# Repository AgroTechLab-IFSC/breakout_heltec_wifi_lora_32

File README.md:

# Breakout Board for Heltec WiFi Lora 32
Breakout board for [Heltec WiFi LoRa 32](https://docs.heltec.org/en/node/esp32/wifi_lora_32/index.html):
 - [Heltec WiFi LoRa 32 V2 board](https://heltec.org/project/wifi-lora-32v2);
 - [Heltec WiFi LoRa 32 V3 board](https://heltec.org/project/wifi-lora-32-v3);

## PCB Features
The breakout PCB has a dimension of 100mm x 100mm and 2 layers.

Project files:
 - [Schematic](./schematic.pdf)
 - [Gerber](./gerber.zip)

## 3D Images

## PCB Images

<div style="text-align:center;">
   <br><hr>
   <p>All rights reserved. &copy; Since 2020.<br>
   <b><a href="https://agrotechlab.lages.ifsc.edu.br/">AgroTechLab (<i>Agribusiness Technology Development Laboratory</i>)</a></b><br>
   <b><a href="https://ifsc.edu.br/web/campus-lages">IFSC (<i>Federal Institute of Santa Catarina</i>) - Campus Lages</a></b><br>
   225 Heitor Vila Lobos St., San Francisco<br>
   Lages/SC - Brazil<br>
   88506-400</p>
</div>

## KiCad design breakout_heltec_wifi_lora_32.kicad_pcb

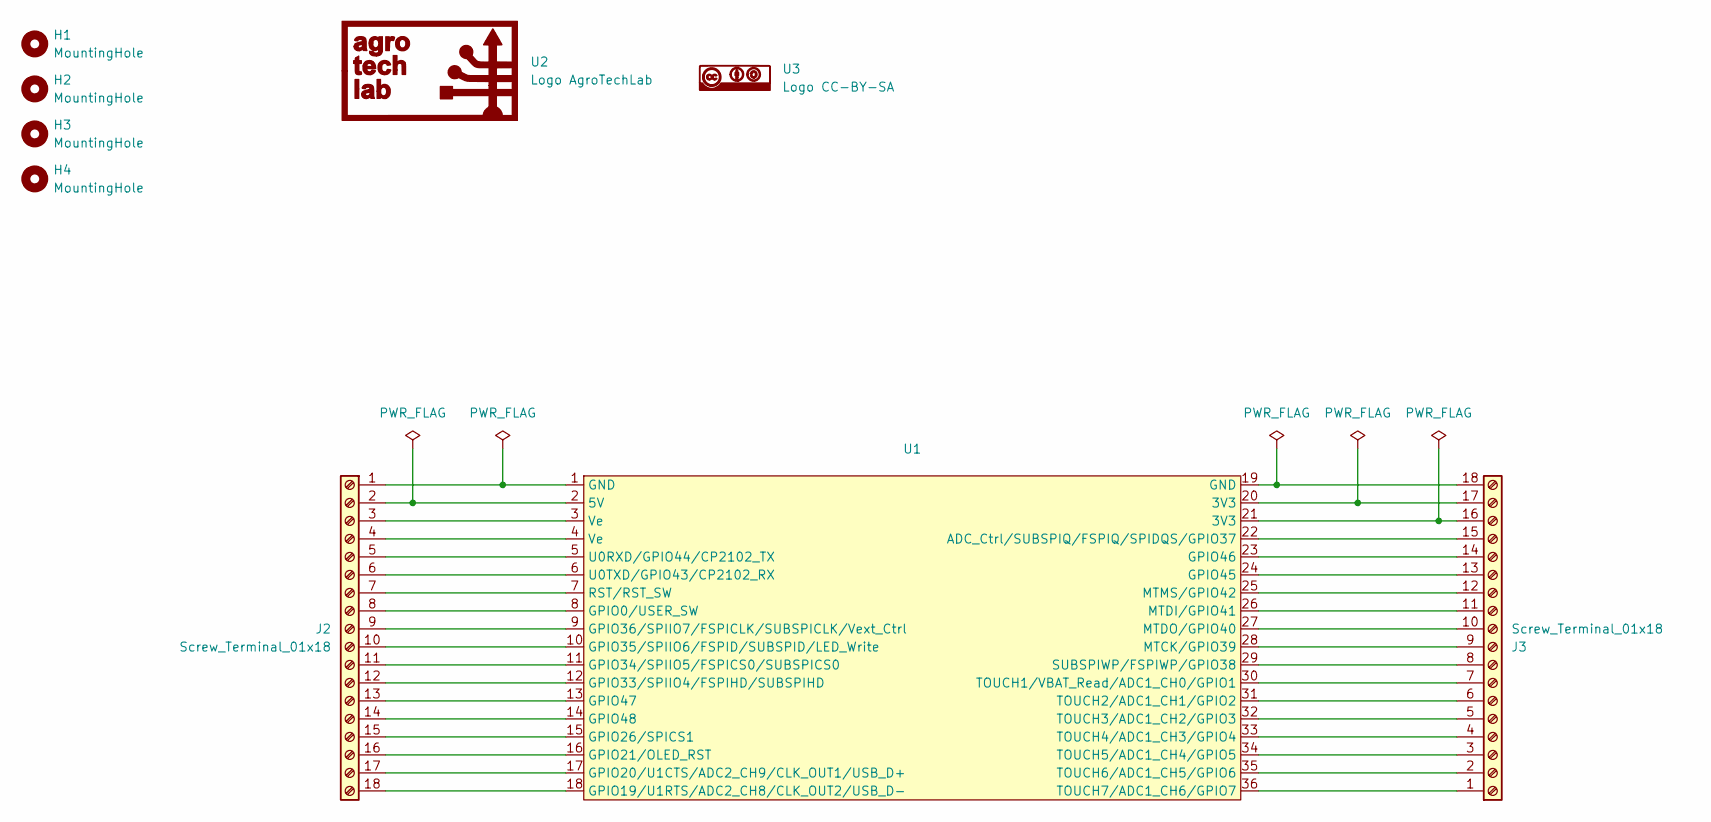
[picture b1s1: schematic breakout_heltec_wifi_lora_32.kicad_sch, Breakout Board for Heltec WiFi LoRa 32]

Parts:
H1, H2, H3, H4: MountingHole; MountingHole_3.2mm_M3_Pad_Via
J2, J3: Screw_Terminal_01x18; TE_1-282856-8
U1: Heltec WiFi LoRa 32 V3
U2: Logo AgroTechLab
U3: Logo CC-BY-SA

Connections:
unnamed: J2.1, U1.1 (GND)
unnamed: J2.2, U1.2 (5V)
unnamed: J2.3, U1.3 (Ve)
unnamed: J2.4, U1.4 (Ve)
unnamed: J2.5, U1.5 (U0RXD/GPIO44/CP2102_TX)
unnamed: J2.6, U1.6 (U0TXD/GPIO43/CP2102_RX)
unnamed: J2.7, U1.7 (RST/RST_SW)
unnamed: J2.8, U1.8 (GPIO0/USER_SW)
unnamed: J2.9, U1.9 (GPIO36/SPIIO7/FSPICLK/SUBSPICLK/Vext_Ct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)
unnamed: J2.10, U1.10 (GPIO35/SPIIO6/FSPID/SUBSPID/LED_Write)
unnamed: J2.11, U1.11 (GPIO34/SPIIO5/FSPICS0/SUBSPICS0)
unnamed: J2.12, U1.12 (GPIO33/SPIIO4/FSPIHD/SUBSPIHD)
unnamed: J2.13, U1.13 (GPIO47)
unnamed: J2.14, U1.14 (GPIO48)
unnamed: J2.15, U1.15 (GPIO26/SPICS1)
unnamed: J2.16, U1.16 (GPIO21/OLED_RST)
unnamed: J2.17, U1.17 (GPIO20/U1CTS/ADC2_CH9/CLK_OUT1/USB_D+)
unnamed: J2.18, U1.18 (GPIO19/U1RTS/ADC2_CH8/CLK_OUT2/USB_D-)
unnamed: J3.1, U1.36 (TOUCH7/ADC1_CH6/GPIO7)
unnamed: J3.2, U1.35 (TOUCH6/ADC1_CH5/GPIO6)
unnamed: J3.3, U1.34 (TOUCH5/ADC1_CH4/GPIO5)
unnamed: J3.4, U1.33 (TOUCH4/ADC1_CH3/GPIO4)
unnamed: J3.5, U1.32 (TOUCH3/ADC1_CH2/GPIO3)
unnamed: J3.6, U1.31 (TOUCH2/ADC1_CH1/GPIO2)
unnamed: J3.7, U1.30 (TOUCH1/VBAT_Read/ADC1_CH0/GPIO1)
unnamed: J3.8, U1.29 (SUBSPIWP/FSPIWP/GPIO38)
unnamed: J3.9, U1.28 (MTCK/GPIO39)
unnamed: J3.10, U1.27 (MTDO/GPIO40)
unnamed: J3.11, U1.26 (MTDI/GPIO41)
unnamed: J3.12, U1.25 (MTMS/GPIO42)
unnamed: J3.13, U1.24 (GPIO45)
unnamed: J3.14, U1.23 (GPIO46)
unnamed: J3.15, U1.22 (ADC_Ctrl/SUBSPIQ/FSPIQ/SPIDQS/GPIO37)
unnamed: J3.16, U1.21 (3V3)
unnamed: J3.17, U1.20 (3V3)
unnamed: J3.18, U1.19 (GND)

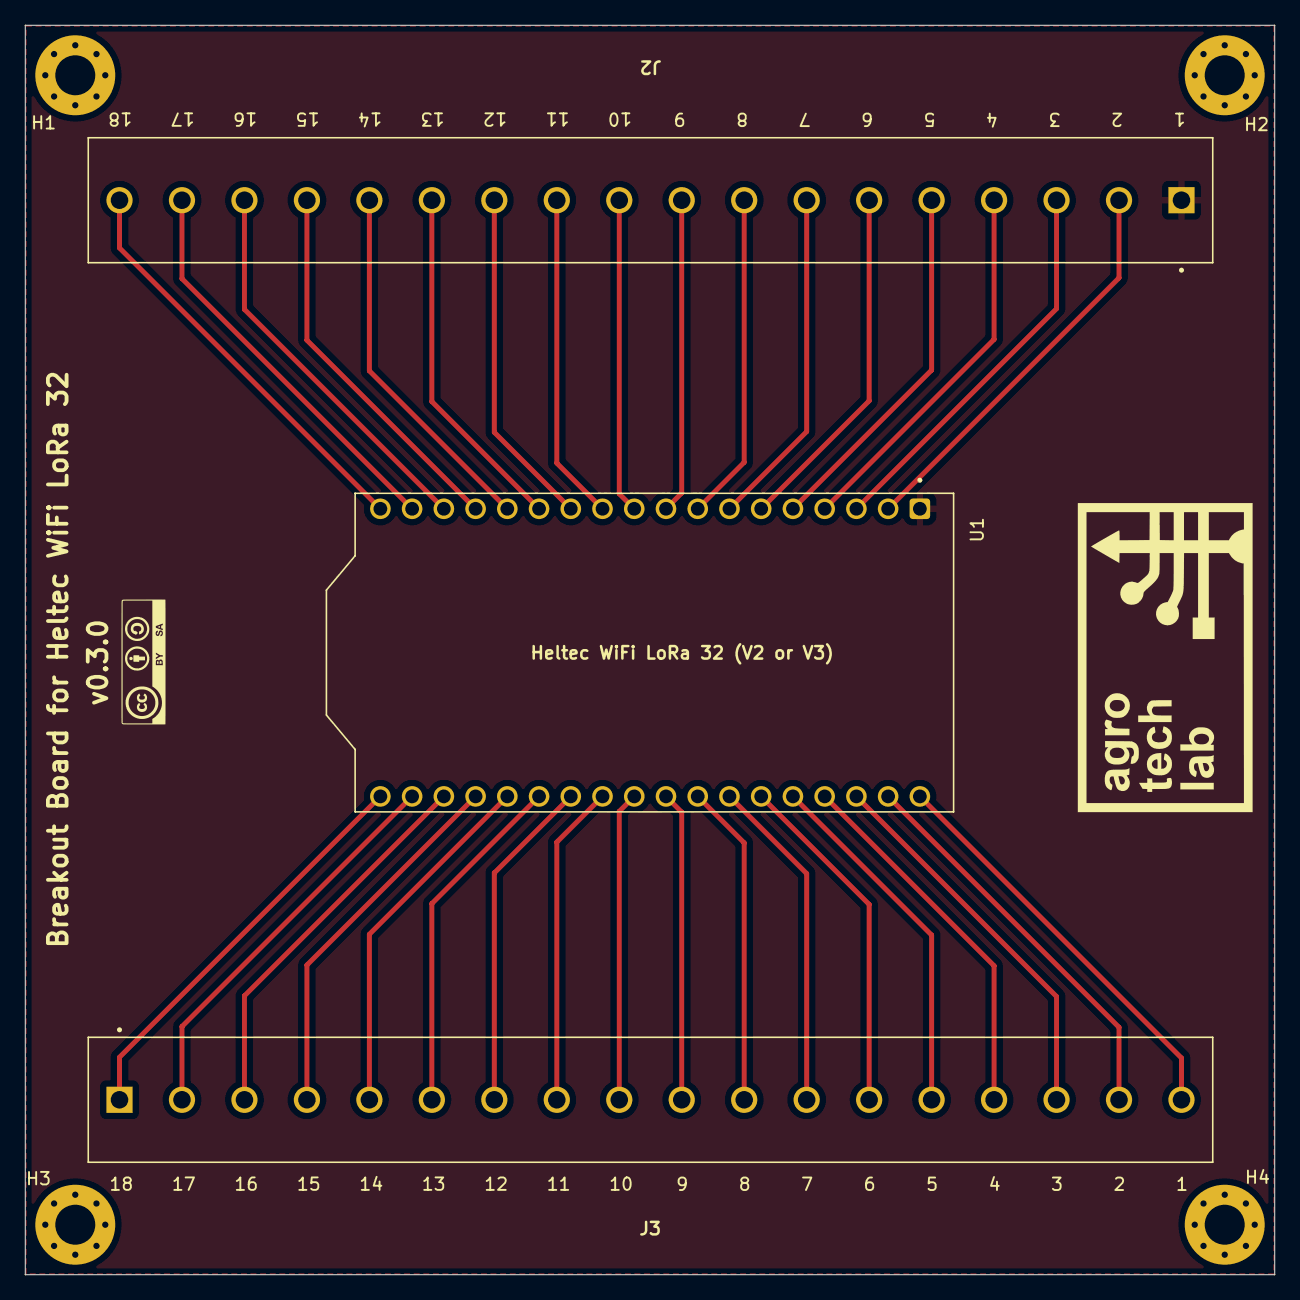
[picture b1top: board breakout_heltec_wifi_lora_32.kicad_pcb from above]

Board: 2 copper layers, 100.0 x 100.0 mm, 9 parts (0 on the bottom side), 36 nets.

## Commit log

2025-05-26 docs: Create project documentation #1
2025-05-27 feat: Create breakout schematic #2
2025-05-27 feat: Create breakout board PCB layout #3
2025-05-27 docs: Create multiple 3D views #4
2025-05-27 build: Create gerber files and release #5
2025-05-31 feat: Integrate Heltec Wifi LoRa 32 V3 into the breakout board #6
2025-06-03 feat: Updated PCB to v0.3.0
2025-09-22 docs: Documentation update
2025-09-22 docs: Update issue templates
2025-09-22 docs: Created pull request template

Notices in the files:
breakout_heltec_wifi_lora_32.kicad_pcb:
Licenced under CC-BY-SA 4.0
